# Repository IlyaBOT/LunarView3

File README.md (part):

# Lunar Dumper / Lunar Writer

Актуальные устройства проекта:

- **[Lunar Dumper](Dumper-Lite/NM27C512_Dumper_Lite.kicad_pro)** — минимальный USB-дампер, 5 В, чтение EPROM. Пользовательская разводка сохранена; обновлены названия и идентификатор прошивки. [Инструкция](Dumper-Lite/README.md), [прошивка 115200](firmware/lite/README.md).
- **[Lunar Writer, Rev. 1](Lunar-Writer/Lunar_Writer.kicad_pro)** — новая полностью разведённая двухслойная плата **150×105 мм**, ATmega/CH340/DIP-28, буфер данных, коммутация VCC/VPP и отдельная винтовая клемма **12–24 В DC**. [Описание и настройка](Lunar-Writer/README.md), [схема PDF](Lunar-Writer/Lunar_Writer_Schematic.pdf), [3D](Lunar-Writer/Writer_3D.png), [Gerber/drill](Lunar-Writer/production/). ERC/DRC/соответствие схеме: 0 замечаний; 0 неразведённых связей. Аппаратная наладка ещё не выполнена, штатная WRITE заблокирована.
- **[LunarView 3, 1.2](app-win_forms/README.md)** — Windows Forms: чтение, HEX/ASCII, открытие ROM-файлов и сравнение. Сборка: `app-win_forms/release/LunarView3.exe`. Сейчас работает с протоколом Lunar Dumper; Writer обслуживается прежней утилитой `tools/eprom_tool.py`, 57600 бод.
- **[Адаптер КР573РФ5](Adapter-KR573RF5/README.md)** — отдельная плата только для чтения, не для программирования через Writer.
- [Изготовление фоторезистом](docs/PCB_Photoresist_RU.md), [источники 3D-моделей](docs/3D_Models_RU.md).

Проверка от 12.10.2026: новую плату Writer проверили отдельно. У сохранённого пользовательского Dumper остаются прежние 2 неразведённые связи и 16 предупреждений (15 изолированных участков меди, 1 незавершённая дорожка); переименование их не изменило. До домашнего изготовления Dumper следует закончить эту проверку. Медные слои и геометрия Dumper при работе над Writer не менялись; доказательство — `validation/lunar-products-2026-10-12/rename-audit.json`.

Файлы `NM27C512_Dumper.*` в корне и `baseline_readonly/` сохранены как исторические проекты Stage 2 / раннего read-only. Полноценный актуальный программатор открывается из **Lunar-Writer**. Ниже приведены сведения старой Stage 2: там J4 являлся входом готового VPP, а повышающего преобразователя не было. Для нового питания и калибровки Writer используйте его README.

## Historical Stage 2 architecture

```mermaid
flowchart LR
    USB[USB Micro-B 5 V] --> F[F1 and 5 V logic rail]
    USB --> CH[CH340C USB UART]
    CH <--> AVR[ATmega328P 16 MHz]
    AVR --> SR[U2/U3/U4 74HC595 chain]
    SR --> A[A0-A19 and RGB status]
    AVR <--> H[Protected HCT245 data bus]
    H <--> ROM[U6 NM27C512 or one J_TARGET adapter]
    A --> ROM
    EXT[External regulated VPP] --> ARM[Q3 PMOS arming stage]
    ARM --> PULSE[Q7 final VPP switch]
    EXT --> REG[LM317 6.25 V]
    REG --> K[K1 default-READ DPDT relay]
    PULSE --> K
    F --> K
    K --> ROM
    RESET[RESET and enable gates] --> ARM
    RESET --> PULSE
    AVR --> K
```

USB supplies all 5 V logic, the CH340 and relay. J4 accepts regulated VPP_IN on pin1 and GND on pin2, expected 12.5-25 V depending on the exact profile. +6V25_PROG is generated from that supply with LM317T. K1 selects target +5 V / +6.25 V and separately selects socket pin22 OE logic / VPP_SW. Normal RESET and power-on use the unenergized READ contacts. VPP and elevated target VCC have no direct connection to an AVR GPIO.

Old NMOS EPROMs can have TTL output-high specifications below the AVR's 5 V CMOS input threshold. Stage 2 therefore uses **SN74HCT245DW**, with TTL-compatible inputs; a 74HC245 is not an equivalent substitute here. Both sides have 1k resistors and external BAT54S clamps. The read-only baseline keeps the requested direct NM27C512 data connection. Target outputs during 6.25 V byte verify are clamped on the buffer side. MCU releases its outputs before VPP_DRIVE changes the bus direction.

## ATmega328P-AU TQFP32 map

PB1, originally reserved for an interlock, now explicitly controls HV_ARM_EN. PB4/MISO is used only by ISP. ADC6/ADC7 are analog-only package pins.

| Package pin | Function | Net |
| --- | --- | --- |
| 1 | PD3 | PROG_MODE |
| 2 | PD4 | ROM_D6 |
| 3 | GND | GND |
| 4 | VCC | +5V |
| 5 | GND | GND |
| 6 | VCC | +5V |
| 7 | PB6 / XTAL1 | XTAL1 |
| 8 | PB7 / XTAL2 | XTAL2 |
| 9 | PD5 | ROM_D7 |
| 10 | PD6 | TARGET_CE_PGM# |
| 11 | PD7 | TARGET_OE# |
| 12 | PB0 | TARGET_PGM# |
| 13 | PB1 | HV_ARM_EN |
| 14 | PB2 | ADDR_LATCH |
| 15 | PB3 / MOSI | ADDR_SER |
| 16 | PB4 / MISO | ISP_MISO |
| 17 | PB5 / SCK | ADDR_SCK |
| 18 | AVCC | +5V |
| 19 | ADC6 | VPP_SENSE |
| 20 | AREF | AREF |
| 21 | GND | GND |
| 22 | ADC7 | TARGET_VCC_SENSE |
| 23 | PC0 | ROM_D0 |
| 24 | PC1 | ROM_D1 |
| 25 | PC2 | ROM_D2 |
| 26 | PC3 | ROM_D3 |
| 27 | PC4 | ROM_D4 |
| 28 | PC5 | ROM_D5 |
| 29 | PC6 / RESET | RESET |
| 30 | PD0 / RXD | UART_RX |
| 31 | PD1 / TXD | UART_TX |
| 32 | PD2 | VPP_EN |

## Address and status chain

U2 SER is PB3/MOSI. U2 Q7S (pin9) goes to U3 SER (pin14), then U3 Q7S to U4 SER. All three share pin11 SRCLK=ADDR_SCK/PB5 and pin12 RCLK=ADDR_LATCH/PB2; SRCLR# pin10=+5V, OE# pin13=GND, VCC16=+5V and GND8=GND. R7 pulls LATCH down during RESET/ISP, keeping ISP shifts from latching. CE/OE/PGM pull-ups keep the target inactive while addresses are unspecified at initial power-up.

| Output | U2 | U3 | U4 |
|---|---|---|---|
| Q0 / pin15 | A0 | A8 | A16 |
| Q1 / pin1 | A1 | A9 | A17 |
| Q2 / pin2 | A2 | A10 | A18 |
| Q3 / pin3 | A3 | A11 | A19 |
| Q4 / pin4 | A4 | A12 | STATUS_RED |
| Q5 / pin5 | A5 | A13 | STATUS_GREEN |
| Q6 / pin6 | A6 | A14 | STATUS_BLUE |
| Q7 / pin7 | A7 | A15 | NC / reserved |

Send U4 byte first, U3 next and U2 last, MSB first, then latch. The high byte's low nibble is A16-A19; bits4/5/6 are active-low RGB R/G/B; bit7 remains LOW. Firmware preserves RGB state on every address update and masks unused upper addresses LOW for smaller profiles. The baseline sends only U3 then U2.

## Direct U6 socket: NM27C512 DIP28

Use only a correctly oriented NM27C512 or verified compatible read part in U6. Footprint is `Package_DIP:DIP-28_W15.24mm_Socket_LongPads`; it suits a conventional 600 mil socket. Verify the selected ZIF socket's body/lever clearance before PCB layout rather than assuming every ZIF is mechanically identical.

| Pin | Net | Pin | Net |
| --- | --- | --- | --- |
| 1 | A15 | 28 | TARGET_VCC |
| 2 | A12 | 27 | A14 |
| 3 | A7 | 26 | A13 |
| 4 | A6 | 25 | A8 |
| 5 | A5 | 24 | A9 |
| 6 | A4 | 23 | A11 |
| 7 | A3 | 22 | SOCKET_OE_VPP |
| 8 | A2 | 21 | A10 |
| 9 | A1 | 20 | TARGET_CE_PGM# |
| 10 | A0 | 19 | TARGET_D7 |
| 11 | TARGET_D0 | 18 | TARGET_D6 |
| 12 | TARGET_D1 | 17 | TARGET_D5 |
| 13 | TARGET_D2 | 16 | TARGET_D4 |
| 14 | GND | 15 | TARGET_D3 |

In READ, TARGET_VCC=+5V and SOCKET_OE_VPP follows TARGET_OE#. In PROGRAM, TARGET_VCC=+6.25V and SOCKET_OE_VPP=VPP_SW. Pin20 CE/PGM# is the programming-pulse input. R2/R3/R8 pull CE/OE/PGM HIGH from the logic rail during RESET. K1 physically disconnects the MCU OE path from VPP.

## Headers and UART

J2 is the standard AVR ISP 2x3: pin1 MISO, 2 +5V, 3 SCK, 4 MOSI, 5 RESET, 6 GND. J3 is a 1x3 header: **1 GND, 2 RX (MCU PD0), 3 TX (MCU PD1)**. An external UART TX goes to J3 RX and external RX to J3 TX. Use 5 V TTL and avoid simultaneous active TX sources.

CH340C TXD pin2 goes through R4=1k to MCU RX; MCU TX goes through R5=1k to CH340 RXD pin3. WCH pins: 1 GND, 4 V3 (C3 only), 5 UD+, 6 UD-, 7 NC, 8 OUT#/optional DTR2 (unused), 9 CTS#, 10 DSR#, 11 RI#, 12 DCD#, 13 DTR#, 14 RTS#, 15 R232=GND, 16 VCC=+5V. Every unused output/input has an explicit NC marker. CH340C has an internal oscillator: there is no 12 MHz crystal.

DTR# reaches RESET through C13=100nF, not directly. R1 is the 10k 0603 pull-up, SW1 resets to GND, and ISP RESET is the same net. D9 clamps a positive DTR-release spike on RESET, which also feeds the 5 V interlock inputs.

J1 uses `Connector_USB:USB_Micro-B_Molex-105017-0001`; buy that pad-compatible receptacle. Pins1/2/3/4/5 are VBUS/D-/D+/NC/GND. Shield pad SH=GND. USB VBUS reaches the logic rail through the 1812 500 mA hold polyfuse. The complete circuit can exceed 100 mA, especially with an old EPROM and the 100 mA relay coil. Use a stable USB source whose permitted current covers the load; assess USB descriptor/current and inrush compliance during product engineering. The polyfuse is not an active inrush limiter.

## J_TARGET 2x20 expansion pinout

Odd numbers are the symbol's left column; even numbers are right. Data pins expose the protected **target side** of U9, not the bare MCU pins. Populate U6 or one adapter, never both.

| Odd pin | Net | Even pin | Net |
| --- | --- | --- | --- |
| 1 | A0 | 2 | A1 |
| 3 | A2 | 4 | A3 |
| 5 | A4 | 6 | A5 |
| 7 | A6 | 8 | A7 |
| 9 | A8 | 10 | A9 |
| 11 | A10 | 12 | A11 |
| 13 | A12 | 14 | A13 |
| 15 | A14 | 16 | A15 |
| 17 | A16 | 18 | A17 |
| 19 | A18 | 20 | A19 |
| 21 | TARGET_D0 | 22 | TARGET_D1 |
| 23 | TARGET_D2 | 24 | TARGET_D3 |
| 25 | TARGET_D4 | 26 | TARGET_D5 |
| 27 | TARGET_D6 | 28 | TARGET_D7 |
| 29 | TARGET_CE_PGM# | 30 | TARGET_OE# |
| 31 | TARGET_PGM# | 32 | VPP_SW |
| 33 | TARGET_VCC | 34 | +5V |
| 35 | +6V25_PROG | 36 | GND |
| 37 | PROG_MODE | 38 | GND |
| 39 | RESET | 40 | GND |

Adapters are device-specific. The three reference sheets document 24/28/32-pin roles without adding multiple live EPROM loads. Separate VPP pins often need +5 V in READ, so do not tie them to an unpowered VPP_SW. Future programming adapters require appropriately rated switching or keyed jumpers; the onboard K1 switches U6 pin22 only. RF5 mapping is intentionally withheld pending a manufacturer source.

## VPP, relay and regulator details

Q3 IRF9540N is a 100 V P-channel TO220 device, G1/D2/S3. R30 pulls gate to source; Q4 pulls the gate through R31=2.2k. D5's cathode is SOURCE/VPP_IN and anode is GATE, limiting |VGS| to approximately 10 V. The gate resistor is 1206 / at least 0.25 W for the worst input, instead of overstressing a small resistor. U10 gates PB1 with RESET for arming; U8 gates PD2 with RESET for the final VPP switch. Pull-downs keep both OFF when AVR pins float. No onboard 5-to-25 V boost is present.

The slow PMOS arms an internal node; Q7 MMBT5401 / Q6 MMBT5551 provide the separate final VPP switch. This is a prototype pulse-stage choice; its <=50 ns OE/VPP rise requirement is **unverified** and must be measured before WRITE is commissioned. Its voltage drop must be calibrated at load. No bulk cap sits on VPP_SW; R37=10k discharges it. D6 and two 5.1k resistors indicate actual switched VPP independently of the software RGB LED.

K1 standard G5V-2-DC5 uses coil pins1/16, COM4-NC6-NO8 for VCC and COM13-NC11-NO9 for OE/VPP. Q5 drives the 100 mA coil; R42=470 ohm gives roughly 9 mA base drive. This replaces the suggested 10k value, which would not establish saturation for that coil. D8 is the 1N4148WS SOD323 flyback diode, cathode on +5V.

LM317T pin1 ADJ, 2 OUT, 3 IN. R40=120 ohm, R41=430 ohm and RV1=100 ohm set +6V25_PROG. Measure and adjust TP_6V25 to 6.250 V, then verify under load. Approximately 48 ohm of trim is nominal; real reference/Iadj vary. A heatsink is needed for the intended high-input/load combination. Details and acceptance tests are in [bringup.md](docs/bringup.md).

## Voltage monitoring

ADC6 divider is 120k/22k, both 1%, with 10nF at the node: `Vadc = VPP_SW * 22 / 142`. ADC7 is a 10k/10k, 1% divider with 10nF: 5 V target gives 2.500 V and 6.25 V gives 3.125 V. D30/D31 add external Schottky clamps at the ADC nodes.

| VPP_SW, V | Nominal ADC6, V |
| --- | --- |
| 12.75 | 1.975352 |
| 21 | 3.253521 |
| 25 | 3.873239 |
| 30 | 4.647887 |

At 30 V, worst 1% divider tolerance (118.8k top / 22.22k bottom) gives 4.726989 V, below the firmware's 4.75 V minimum logic rail. Normal external supply maximum is 25 V. These are divider ratings, not permitted NM27C512 programming voltages. The calibrated ADC must enforce that profile's much narrower 12.50-13.00 V window. ADC filtering cannot certify transient overshoot; the socket waveform must be scoped.

## Indicators and test points

| Indicator | Meaning |
|---|---|
| D2 GREEN | READ / VERIFY state |
| D2 RED | WRITE state |
| D2 AMBER | IDLE (red and green) |
| D2 BLUE | Transfer/program error state |
| D3 BLUE | Actual UART RX LOW bits via Q1 |
| D4 ORANGE | Actual UART TX LOW bits via Q2 |
| D6 RED | Actual VPP_SW present |

D2 uses the project-local combined common-anode RGB footprint: square SMD KAAF-5050RGBS-13 or four-lead THT WP154A4SEJ3VBDZGW/CA. Populate **one LED only**. Logical pad numbering is 1R/2A/3G/4B; manufacturer numbering differs. See [mounting and pin mapping](docs/RGB_Mounting.md). Each colour has 1k to the relevant 595 output, LOW=ON. Q1/Q2 MMBT3906 emitters are +5V; 10k base resistors limit UART loading to roughly 0.4 mA during LOW bits and LEDs are OFF at idle HIGH. Their collectors drive LEDs through 1k; they do not put a heavy direct LED load on UART.

TP1-TP13 are respectively 5V, GND, 6V25, VPP_IN, VPP_SW, RESET, ADDR_SCK, ADDR_LATCH, CE, OE, PGM, RX and TX. Each is named on its schematic page and is a 1.5 mm pad footprint.

## Device support matrix

The hardware column describes routed schematic capability; no adapter or board has been physically validated. Read verification and algorithm verification have separate source/implementation meanings.

| Device profile | KiB | Address bits | Hardware electrically supported (schematic) | Read profile | Programming algorithm |
| --- | --- | --- | --- | --- | --- |
| NM27C512 | 64 | 16 | Yes, U6 | Enabled | Verified; default bench lock |
| 27C512 | 64 | 16 | Yes, U6 | Enabled | Disabled |
| INTEL2716 | 2 | 11 | Yes, matching adapter | Enabled | Disabled |
| INTEL2732 | 4 | 12 | Yes, matching adapter | Enabled | Disabled |
| INTEL2764 | 8 | 13 | Yes, matching adapter | Enabled | Disabled |
| INTEL27128A | 16 | 14 | Yes, matching adapter | Enabled | Disabled |
| INTEL27256 | 32 | 15 | Yes, matching adapter | Enabled | Disabled |
| KR573RF5 | 2 | 11 | Pending pinout | Disabled/pending | Disabled |
| NM27C010 | 128 | 17 | Yes, matching adapter | Enabled | Disabled |
| NM27C020 | 256 | 18 | Yes, matching adapter | Enabled | Disabled |
| NM27C040 | 512 | 19 | Yes, matching adapter | Enabled | Disabled |
| NM27C080 | 1024 | 20 | Address/pin-role basis | Disabled/pending | Disabled |

2708 is unsupported: its normal read needs +12 V and -5 V in addition to +5 V. 27C160 is unsupported: it requires a 16-bit bus. Different manufacturers' programming rails/polarities/timings must be separate profiles; generic aliases do not authorize WRITE.

## Firmware and host use

Bare-metal AVR C implements INFO, LIST, READ, VERIFY, WRITE and VOLTAGES. Profile size/address mask and program voltage/pulse parameters come from the generated flash table. Timer1 generates the nominal 100 us CE pulse; Timer0 handles the timeouts. Watchdog is 1 s. Hardware RESET gates cut both VPP switches even while AVR GPIO state changes; software turns off VPP before returning the relay to READ. Link/CRC/UART errors invoke the safe sequence. [Protocol details](docs/protocol.md) include the frames, keepalive and final whole-image CRC.

Default WRITE is locked. The National algorithm implemented for NM27C512 requires an erased device, 6.25 V VCC, 12.75 V VPP, 100 us pulses with up to 25 attempts, per-byte verify and final comparison at 5 V. The host requires ambient 20-30 C and explicit confirmation. It checks actual switched VPP with the socket isolated before selecting PROGRAM, then target VCC and VPP before pulses. The circuit must pass [bench commissioning](docs/bringup.md) before using a commissioned build. Do not insert/remove devices while either supply is connected.

```powershell
# Build the default read/verify firmware (WRITE locked).
./firmware/build.ps1

# Install the host's serial dependency; listing itself works without pyserial.
python -m pip install -r tools/requirements.txt
python tools/eprom_tool.py list
python tools/eprom_tool.py info --port COM5
python tools/eprom_tool.py voltages --port COM5
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
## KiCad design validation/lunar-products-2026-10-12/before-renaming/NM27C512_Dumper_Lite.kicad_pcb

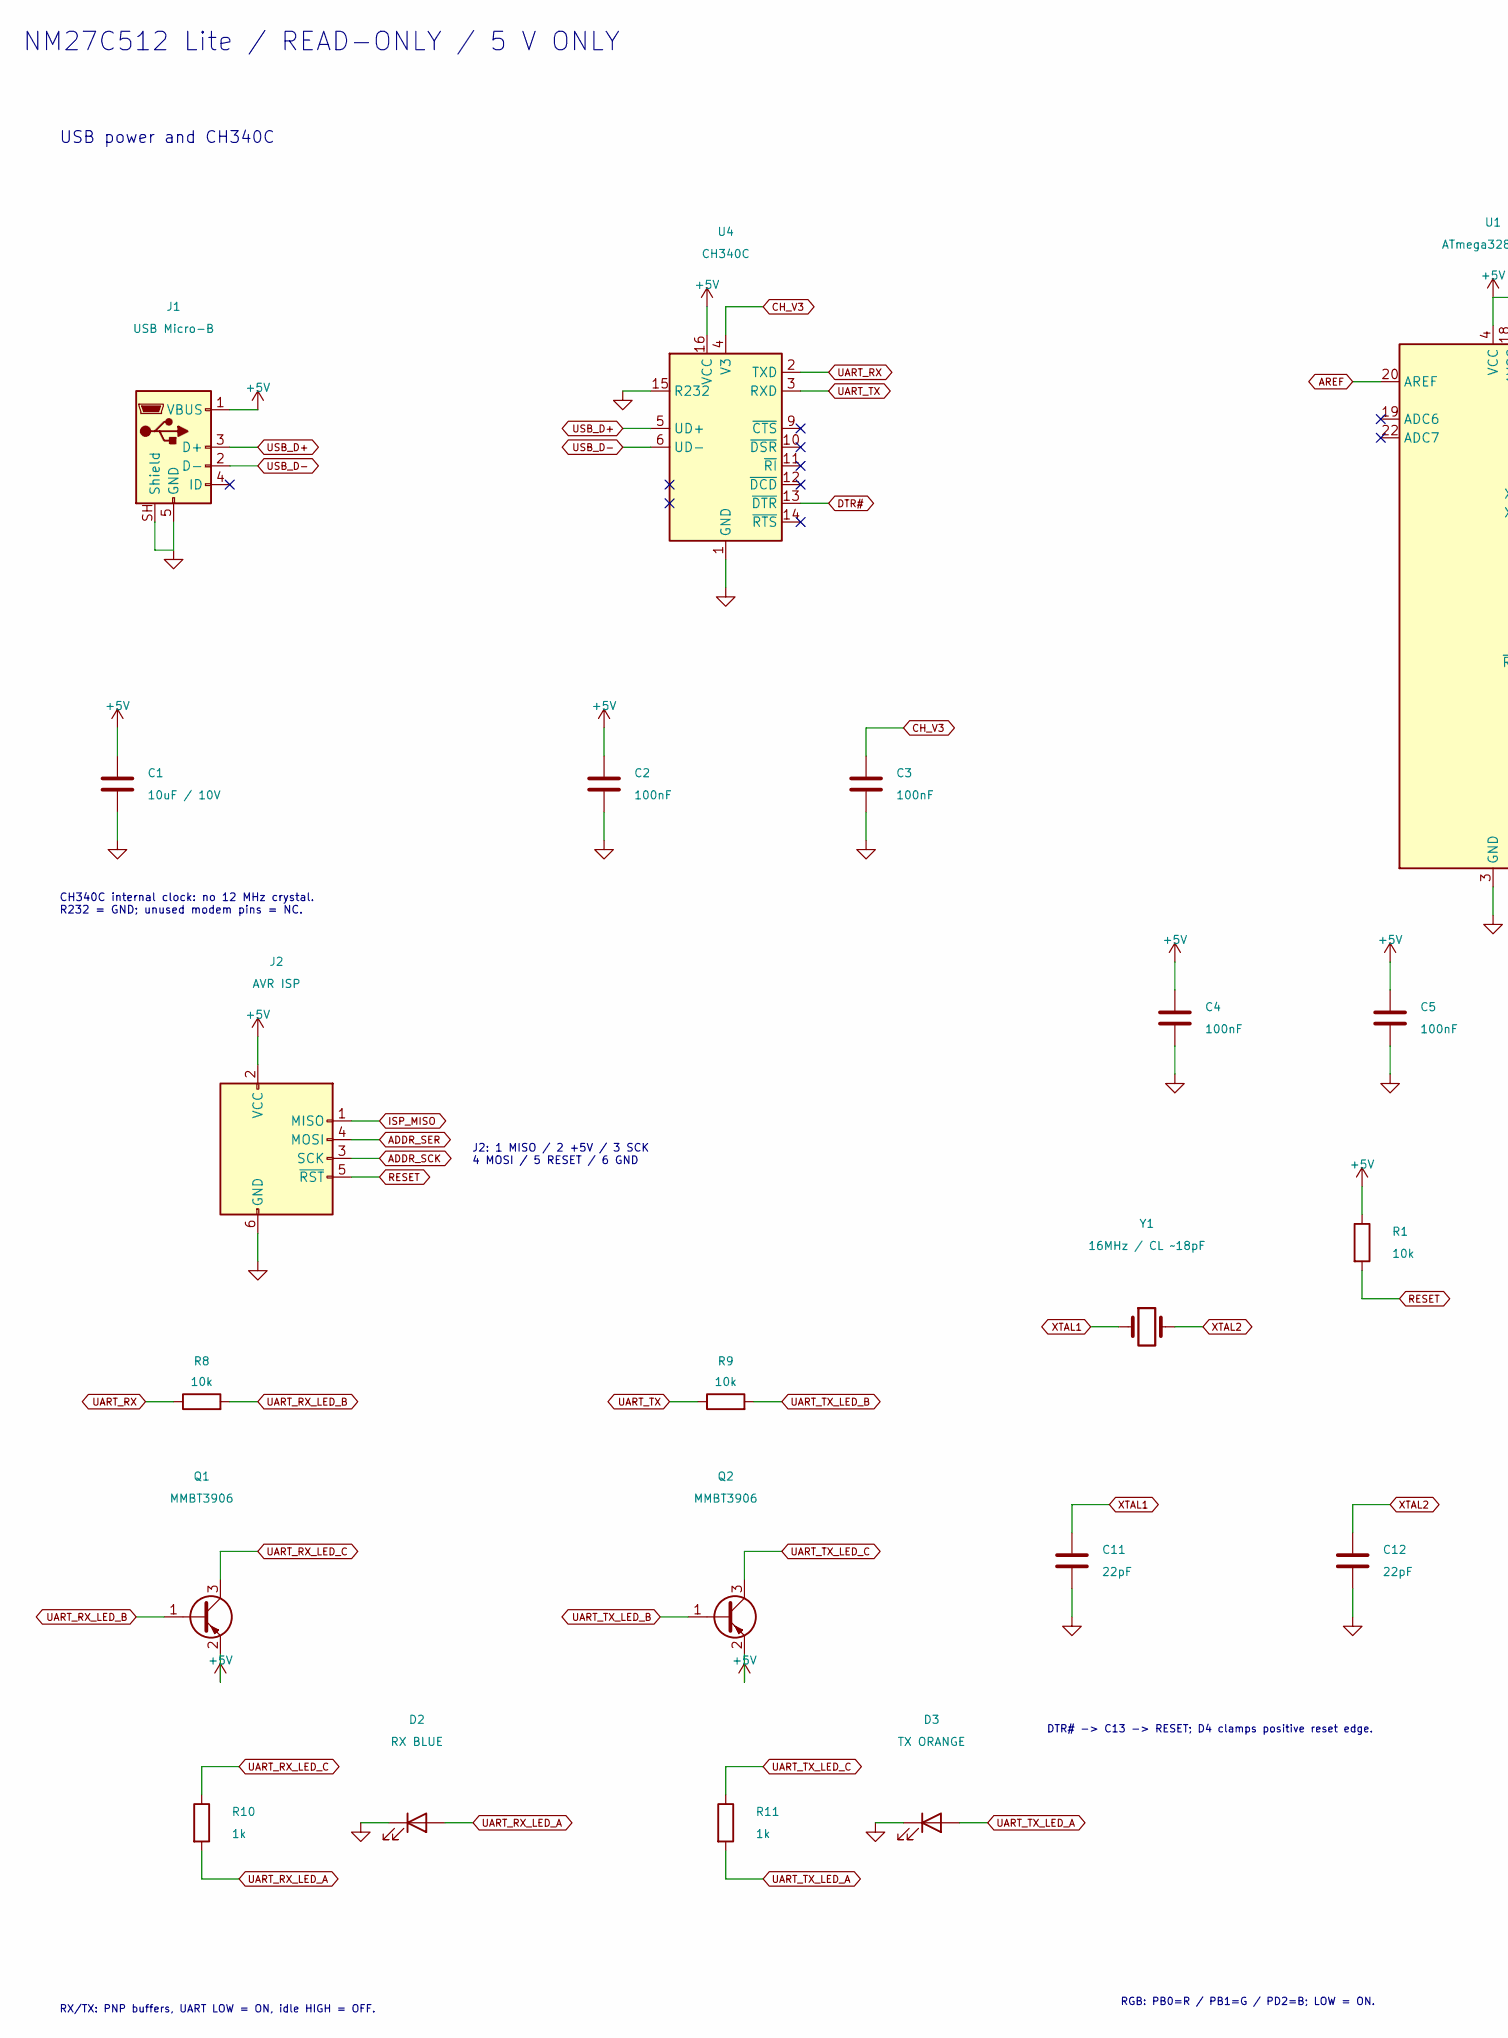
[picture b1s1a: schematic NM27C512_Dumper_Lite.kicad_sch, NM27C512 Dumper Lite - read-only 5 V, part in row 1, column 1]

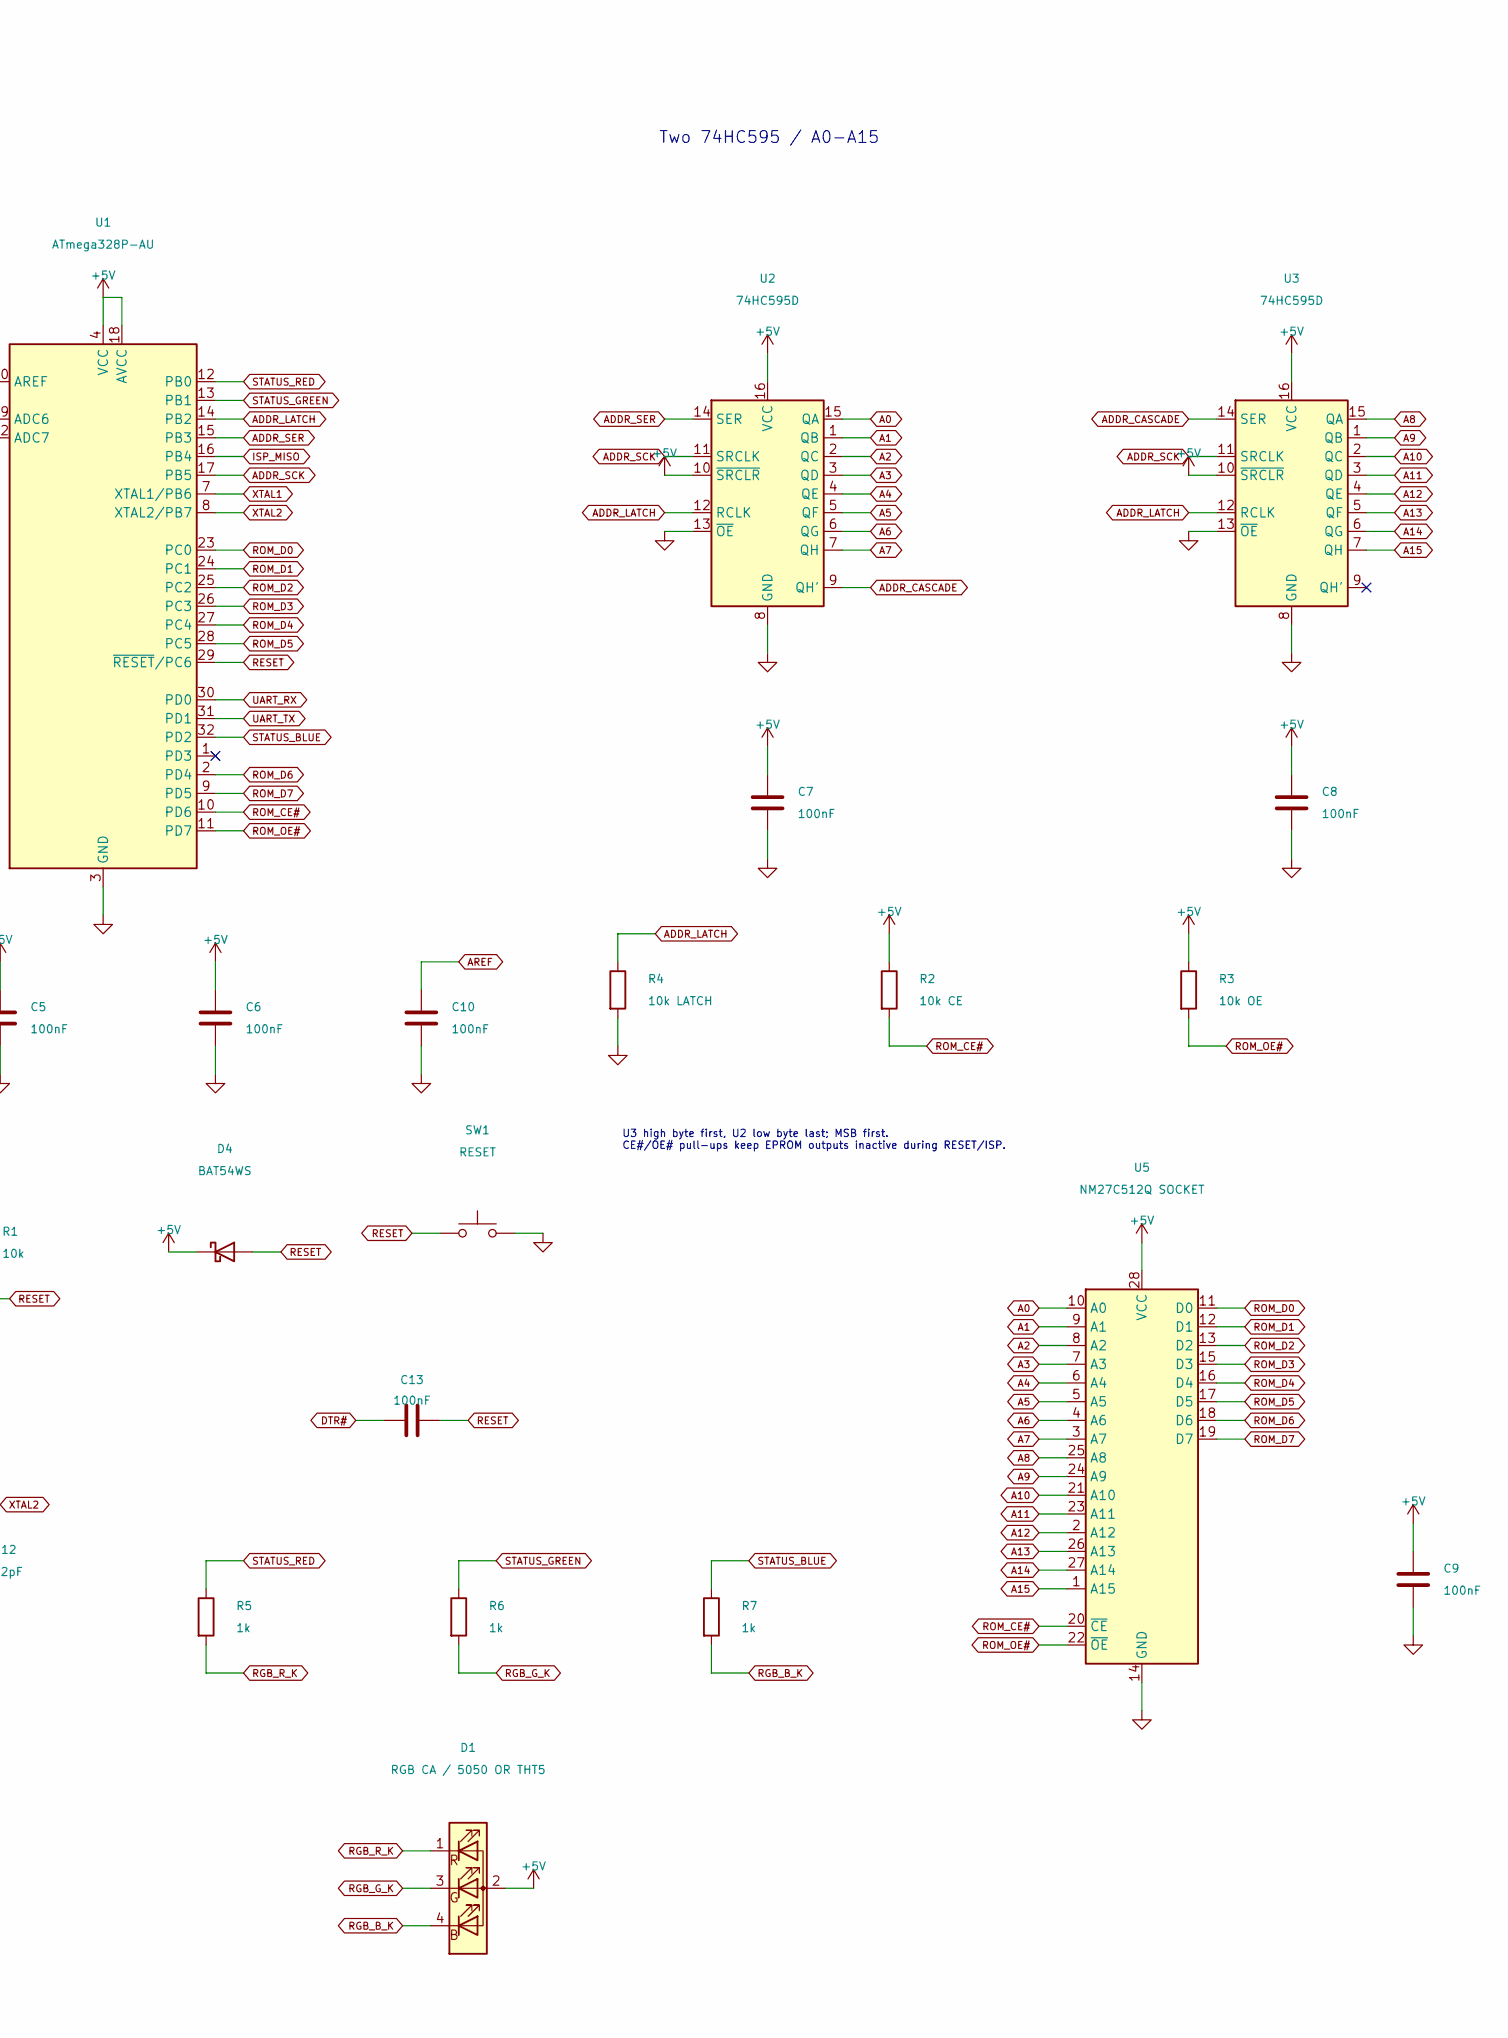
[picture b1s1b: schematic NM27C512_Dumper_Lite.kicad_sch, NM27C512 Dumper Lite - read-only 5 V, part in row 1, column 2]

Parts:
C1: 10uF / 10V; C_0805_2012Metric
C2, C3, C4, C5, C6, C7, C8, C9, C10, C13: 100nF; C_0603_1608Metric
C11, C12: 22pF; C_0603_1608Metric
D1: RGB CA / 5050 OR THT5; RGB_CA_5050_or_THT5
D2: RX BLUE; LED_0603_1608Metric
D3: TX ORANGE; LED_0603_1608Metric
D4: BAT54WS; D_SOD-323
J1: USB Micro-B; USB_Micro-B_Molex-105017-0001
J2: AVR ISP; PinHeader_2x03_P2.54mm_Vertical
Q1, Q2: MMBT3906; SOT-23
R1, R8, R9: 10k; R_0603_1608Metric
R2: 10k CE; R_0603_1608Metric
R3: 10k OE; R_0603_1608Metric
R4: 10k LATCH; R_0603_1608Metric
R5, R6, R7, R10, R11: 1k; R_0603_1608Metric
SW1: RESET; SW_PUSH_6mm
U1: ATmega328P-AU; TQFP-32_7x7mm_P0.8mm
U2, U3: 74HC595D; SOIC-16_3.9x9.9mm_P1.27mm
U4: CH340C; SOIC-16_3.9x9.9mm_P1.27mm
U5: NM27C512Q SOCKET; DIP-28_W15.24mm_Socket_LongPads
Y1: 16MHz / CL ~18pF; Crystal_HC49-4H_Vertical

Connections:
+5V: C1.1, C2.1, C4.1, C5.1, C6.1, C7.1, C8.1, C9.1, D1.2 (A), D4.1 (K), J1.1 (VBUS), J2.2 (VCC), Q1.2 (E), Q2.2 (E), R1.1, R2.1, R3.1, U1.4 (VCC), U1.6 (VCC), U1.18 (AVCC), U2.10 (~SRCLR), U2.16 (VCC), U3.10 (~SRCLR), U3.16 (VCC), U4.16 (VCC), U5.28 (VCC)
A0: U2.15 (QA), U5.10 (A0)
A1: U2.1 (QB), U5.9 (A1)
A2: U2.2 (QC), U5.8 (A2)
A3: U2.3 (QD), U5.7 (A3)
A4: U2.4 (QE), U5.6 (A4)
A5: U2.5 (QF), U5.5 (A5)
A6: U2.6 (QG), U5.4 (A6)
A7: U2.7 (QH), U5.3 (A7)
A8: U3.15 (QA), U5.25 (A8)
A9: U3.1 (QB), U5.24 (A9)
A10: U3.2 (QC), U5.21 (A10)
A11: U3.3 (QD), U5.23 (A11)
A12: U3.4 (QE), U5.2 (A12)
A13: U3.5 (QF), U5.26 (A13)
A14: U3.6 (QG), U5.27 (A14)
A15: U3.7 (QH), U5.1 (A15)
ADDR_CASCADE: U2.9 (QH'), U3.14 (SER)
ADDR_LATCH: R4.1, U1.14 (PB2), U2.12 (RCLK), U3.12 (RCLK)
ADDR_SCK: J2.3 (SCK), U1.17 (PB5), U2.11 (SRCLK), U3.11 (SRCLK)
ADDR_SER: J2.4 (MOSI), U1.15 (PB3), U2.14 (SER)
AREF: C10.1, U1.20 (AREF)
CH_V3: C3.1, U4.4 (V3)
DTR#: C13.1, U4.13 (~DTR)
GND: C1.2, C2.2, C3.2, C4.2, C5.2, C6.2, C7.2, C8.2, C9.2, C10.2, C11.2, C12.2, D2.1 (K), D3.1 (K), J1.5 (GND), J1.SH (Shield), J2.6 (GND), R4.2, SW1.2, U1.3 (GND), U1.5 (GND), U1.21 (GND), U2.8 (GND), U2.13 (~OE), U3.8 (GND), U3.13 (~OE), U4.1 (GND), U4.15 (R232), U5.14 (GND)
ISP_MISO: J2.1 (MISO), U1.16 (PB4)
RESET: C13.2, D4.2 (A), J2.5 (~RST), R1.2, SW1.1, U1.29 (~RESET/PC6)
RGB_B_K: D1.4 (B), R7.2
RGB_G_K: D1.3 (G), R6.2
RGB_R_K: D1.1 (R), R5.2
ROM_CE#: R2.2, U1.10 (PD6), U5.20 (~CE)
ROM_D0: U1.23 (PC0), U5.11 (D0)
ROM_D1: U1.24 (PC1), U5.12 (D1)
ROM_D2: U1.25 (PC2), U5.13 (D2)
ROM_D3: U1.26 (PC3), U5.15 (D3)
ROM_D4: U1.27 (PC4), U5.16 (D4)
ROM_D5: U1.28 (PC5), U5.17 (D5)
ROM_D6: U1.2 (PD4), U5.18 (D6)
ROM_D7: U1.9 (PD5), U5.19 (D7)
ROM_OE#: R3.2, U1.11 (PD7), U5.22 (~OE)
STATUS_BLUE: R7.1, U1.32 (PD2)
STATUS_GREEN: R6.1, U1.13 (PB1)
STATUS_RED: R5.1, U1.12 (PB0)
UART_RX: R8.1, U1.30 (PD0), U4.2 (TXD)
UART_RX_LED_A: D2.2 (A), R10.2
UART_RX_LED_B: Q1.1 (B), R8.2
UART_RX_LED_C: Q1.3 (C), R10.1
UART_TX: R9.1, U1.31 (PD1), U4.3 (RXD)
UART_TX_LED_A: D3.2 (A), R11.2
UART_TX_LED_B: Q2.1 (B), R9.2
UART_TX_LED_C: Q2.3 (C), R11.1
USB_D+: J1.3 (D+), U4.5 (UD+)
USB_D-: J1.2 (D-), U4.6 (UD-)
XTAL1: C11.1, U1.7 (XTAL1/PB6), Y1.1
XTAL2: C12.1, U1.8 (XTAL2/PB7), Y1.2

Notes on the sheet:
RX/TX: PNP buffers, UART LOW = ON, idle HIGH = OFF.
RGB: PB0=R / PB1=G / PD2=B; LOW = ON.
U3 high byte first, U2 low byte last; MSB first. CE#/OE# pull-ups keep EPROM outputs inactive during RESET/ISP.
USB power and CH340C
NM27C512 Lite / READ-ONLY / 5 V ONLY
CH340C internal clock: no 12 MHz crystal. R232 = GND; unused modem pins = NC.
Two 74HC595 / A0-A15
DTR# -> C13 -> RESET; D4 clamps positive reset edge.
J2: 1 MISO / 2 +5V / 3 SCK 4 MOSI / 5 RESET / 6 GND

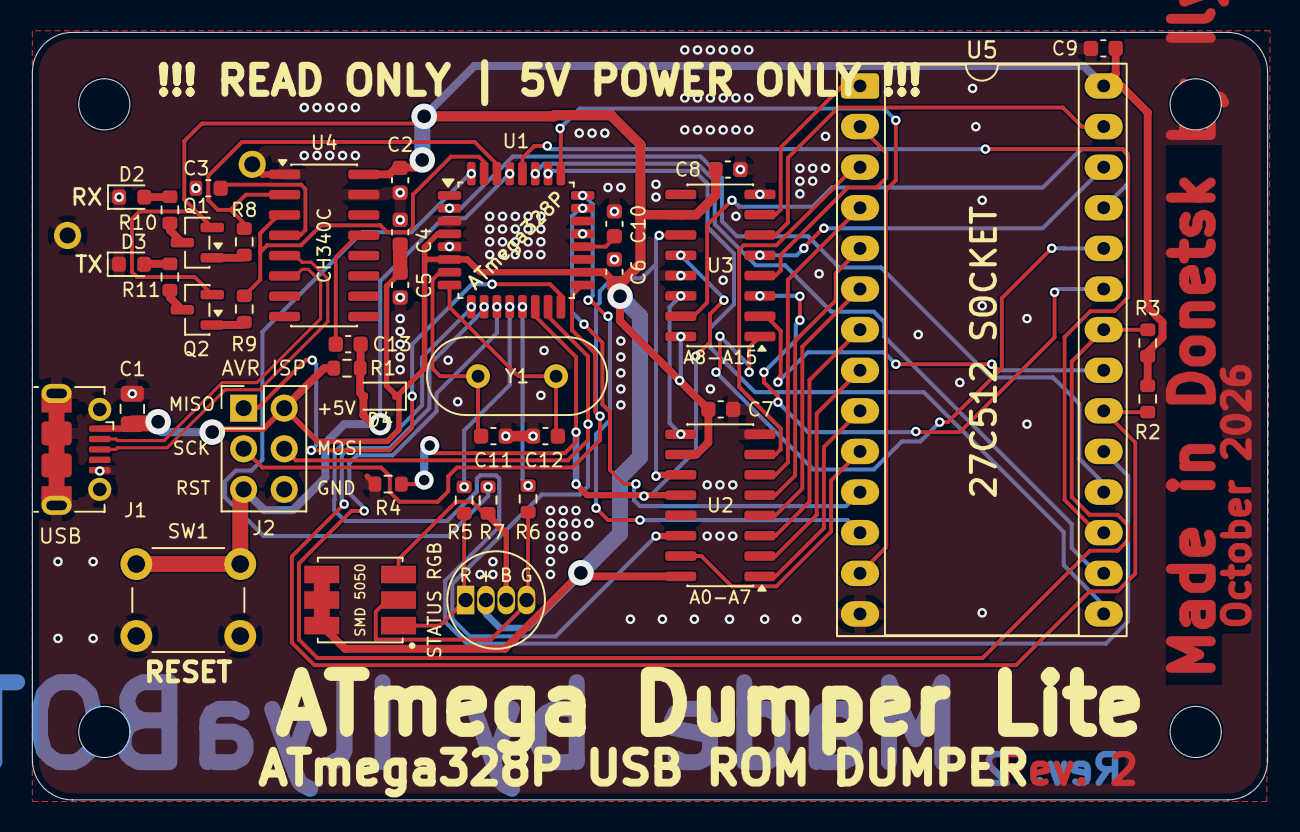
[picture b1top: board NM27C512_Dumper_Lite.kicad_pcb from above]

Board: 2 copper layers, 77.2 x 48.0 mm, 43 parts (0 on the bottom side), 55 nets.

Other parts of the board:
H1, H2, H3, H4: M3 mounting hole; MountingHole_3.2mm_M3

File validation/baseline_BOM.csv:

ref,value,symbol,footprint,sheet
J1,USB Micro-B,Connector:USB_B_Micro,Connector_USB:USB_Micro-B_Molex-105017-0001,controller.kicad_sch
F1,500mA hold,Device:Polyfuse,Fuse:Fuse_1812_4532Metric,controller.kicad_sch
C1,10uF / 10V,Device:C,Capacitor_SMD:C_0805_2012Metric,controller.kicad_sch
U4,CH340C,ProjectSymbols:CH340C_WCH,Package_SO:SOIC-16_3.9x9.9mm_P1.27mm,controller.kicad_sch
C2,100nF,Device:C,Capacitor_SMD:C_0603_1608Metric,controller.kicad_sch
C3,100nF,Device:C,Capacitor_SMD:C_0603_1608Metric,controller.kicad_sch
R4,1k,Device:R,Resistor_SMD:R_0603_1608Metric,controller.kicad_sch
R5,1k,Device:R,Resistor_SMD:R_0603_1608Metric,controller.kicad_sch
U1,ATmega328P-AU,MCU_Microchip_ATmega:ATmega328P-A,Package_QFP:TQFP-32_7x7mm_P0.8mm,controller.kicad_sch
Y1,"16MHz, CL ~18pF",Device:Crystal,Crystal:Crystal_HC49-4H_Vertical,controller.kicad_sch
C11,22pF,Device:C,Capacitor_SMD:C_0603_1608Metric,controller.kicad_sch
C12,22pF,Device:C,Capacitor_SMD:C_0603_1608Metric,controller.kicad_sch
R1,10k,Device:R,Resistor_SMD:R_0603_1608Metric,controller.kicad_sch
SW1,RESET,Switch:SW_Push,Button_Switch_THT:SW_PUSH_6mm,controller.kicad_sch
C13,100nF auto-reset,Device:C,Capacitor_SMD:C_0603_1608Metric,controller.kicad_sch
C4,100nF,Device:C,Capacitor_SMD:C_0603_1608Metric,controller.kicad_sch
C5,100nF,Device:C,Capacitor_SMD:C_0603_1608Metric,controller.kicad_sch
C6,100nF,Device:C,Capacitor_SMD:C_0603_1608Metric,controller.kicad_sch
C10,100nF,Device:C,Capacitor_SMD:C_0603_1608Metric,controller.kicad_sch
J2,AVR ISP,Connector:AVR-ISP-6,Connector_PinHeader_2.54mm:PinHeader_2x03_P2.54mm_Vertical,controller.kicad_sch
J3,UART (MCU RX/TX),Connector_Generic:Conn_01x03,Connector_PinHeader_2.54mm:PinHeader_1x03_P2.54mm_Vertical,controller.kicad_sch
U2,74HC595D,74xx:74HC595,Package_SO:SOIC-16_3.9x9.9mm_P1.27mm,address_target.kicad_sch
C7,100nF,Device:C,Capacitor_SMD:C_0603_1608Metric,address_target.kicad_sch
U3,74HC595D,74xx:74HC595,Package_SO:SOIC-16_3.9x9.9mm_P1.27mm,address_target.kicad_sch
C8,100nF,Device:C,Capacitor_SMD:C_0603_1608Metric,address_target.kicad_sch
R7,10k LATCH pull-down,Device:R,Resistor_SMD:R_0603_1608Metric,address_target.kicad_sch
U5,NM27C512Q SOCKET,Memory_EPROM:27C512,Package_DIP:DIP-28_W15.24mm_Socket_LongPads,address_target.kicad_sch
C9,100nF / 16V,Device:C,Capacitor_SMD:C_0603_1608Metric,address_target.kicad_sch
R2,10k CE pull-up,Device:R,Resistor_SMD:R_0603_1608Metric,address_target.kicad_sch
R3,10k OE pull-up,Device:R,Resistor_SMD:R_0603_1608Metric,address_target.kicad_sch
R6,1k,Device:R,Resistor_SMD:R_0603_1608Metric,address_target.kicad_sch
D1,POWER GREEN,Device:LED,LED_SMD:LED_0603_1608Metric,address_target.kicad_sch

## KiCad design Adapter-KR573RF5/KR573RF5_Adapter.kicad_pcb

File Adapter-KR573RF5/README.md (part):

# Компактный адаптер КР573РФ5 для Dumper Lite

Откройте `KR573RF5_Adapter.kicad_pro`, затем схему или плату. Это отдельный **полностью разведённый двухслойный адаптер 22,86 × 38,10 мм**, только для чтения на 5 В. Сверху — панелька DIP-24, снизу — два ряда круглых контактов «папа» для установки в DIP-28 панельку EPROM дампера. Шаг контактов 2,54 мм, расстояние между рядами 15,24 мм.

## Конструкция и детали

| Поз. | Деталь | Монтаж |
|---|---|---|
| J1 | Два ряда **1×14 круглых штырей**, подходящих для DIP-панельки, шаг 2,54 мм | Снизу, длинные контакты направлены вниз |
| J2 | Панелька DIP-24, 600 mil / 15,24 мм между рядами | Сверху; выемка совпадает с обозначением pin 1 |
| U1 | **SN74HCT245PW**, TSSOP-20, 4,4×6,5 мм, шаг 0,65 мм | Снизу |
| C1 | 100 нФ, X7R, ≥16 В, 0603 | Снизу, возле питания EPROM |
| C2 | 100 нФ, X7R, ≥16 В, 0603 | Снизу, возле питания U1 |
| C3 | 1 мкФ, X7R, ≥10 В, 0603 | Снизу |
| RN1, RN2 | **CAY16-473J4LF**, 4 независимых резистора по 47 кОм в каждой сборке, 3,2×1,6 мм, convex | Снизу; слабые подтяжки данных RF5 к +5 В |

Подойдёт HCT245 другого производителя с **той же распиновкой и TSSOP-20 4,4×6,5 мм**. Не заменяйте на обычный HC245: его входные уровни другие. Точная марка панельки и контактных полос не выбрана; сверяйте шаг, диаметр ножек, высоту и механические габариты перед покупкой. Квадратные штыри 0,64 мм от стандартной гребёнки нельзя силой вставлять в прецизионную DIP-панельку. Наиболее удобны круглые контакты примерно 0,45–0,50 мм или подходящие контакты DIP-переходника, рассчитанные на вашу панельку.

Верхняя панелька смещена на 2,54 мм вправо и на один шаг вниз относительно начала нижнего разъёма. Так её 24 отверстия не совпадают с 28 отверстиями нижнего разъёма и данные можно пропустить через буфер. Нижний буфер находится между рядами контактов. Плата без дополнительных крепёжных отверстий.

Пластиковая опора нижних контактных полос должна обеспечивать зазор **не менее 2,5 мм** между нижней поверхностью адаптера и верхней поверхностью панельки дампера: под адаптером стоят SMD-детали. Выбирайте длину контактов с достаточным рабочим заходом в панельку после учёта этого зазора. Выступающие **сверху** хвосты J1 перед установкой J2 обрежьте заподлицо и проверьте, что они не мешают корпусу J2. Две панельки/полосы изображены габаритными моделями; окончательная механическая совместимость требует проверки реальных деталей.

## Зачем нужен буфер

В опубликованном техническом листке КР573РФ5 указана минимальная выходная «1» 2,55 В. Вход ATmega328P при питании 5 В требует для гарантированной «1» минимум 0,6×VCC, то есть 3 В. Поэтому простая перепайка DIP-24 на DIP-28 не даёт гарантии чтения.

HCT245 принимает TTL-уровни: минимальная входная «1» 2 В по [Texas Instruments SN74HCT245](https://www.ti.com/lit/ds/symlink/sn74hct245.pdf), разделы 5–6. Его выходы питаются от тех же 5 В и подходят для ATmega. Порт A получает данные RF5, порт B подаёт их в дампер; DIR, pin 1, постоянно подключён к +5 В. OE#, pin 19, соединён с OE# EPROM и дампера, поэтому при HIGH буфер отключается. Резисторы подтяжки CE#/OE# уже есть в Lite и повторно на адаптере не установлены. Пороги ATmega: [Microchip ATmega328P, DC characteristics](https://ww1.microchip.com/downloads/aemDocuments/documents/MCU08/ProductDocuments/DataSheets/Atmel-7810-Automotive-Microcontrollers-ATmega328P_Datasheet.pdf).

Когда RF5 отключает свои выходы, восемь входов A буфера всё равно должны иметь определённый уровень. RN1/RN2 задают слабую подтяжку каждого RF5_D0…D7 к +5 В. При выходном LOW нагрузка одного резистора около 0,11 мА; при отключённой EPROM входы буфера остаются HIGH. Используются **изолированные** резисторы 1–8, 2–7, 3–6, 4–5, а не сборка с общей ножкой. Тип, шаг 0,8 мм и габариты проверены по [Bourns CAT/CAY16](https://www.bourns.com/docs/Product-Datasheets/CATCAY.pdf). Посадка KiCad имеет общую ширину земель 2,6 мм, в диапазоне рекомендованных 2,4–2,8 мм для CAY16-J4. На стороне MCU при отключённом буфере следует включить внутренние подтяжки входов данных.

## Распиновка

Нумерация J1 и J2 здесь дана **при взгляде сверху на собранный адаптер**, выемками вверх. Для DIP-28 слева сверху вниз идут 1…14, справа сверху вниз — 28…15. Для DIP-24 слева — 1…12, справа — 24…13. При взгляде на нижнюю сторону левый и правый ряды меняются местами визуально, номера электрических контактов не меняются.

| Вывод J2 / RF5 | Сигнал | Подключение |
|---|---|---|
| 1 | A7 | J1.3 |
| 2 | A6 | J1.4 |
| 3 | A5 | J1.5 |
| 4 | A4 | J1.6 |
| 5 | A3 | J1.7 |
| 6 | A2 | J1.8 |
| 7 | A1 | J1.9 |
| 8 | A0 | J1.10 |
| 9 | D0 | U1.2 → U1.18 → J1.11 |
| 10 | D1 | U1.3 → U1.17 → J1.12 |
| 11 | D2 | U1.4 → U1.16 → J1.13 |
| 12 | GND | J1.14, U1.10 |
| 13 | D3 | U1.5 → U1.15 → J1.15 |
| 14 | D4 | U1.6 → U1.14 → J1.16 |
| 15 | D5 | U1.7 → U1.13 → J1.17 |
| 16 | D6 | U1.8 → U1.12 → J1.18 |
| 17 | D7 | U1.9 → U1.11 → J1.19 |
| 18 | CE# | J1.20 |
| 19 | A10 | J1.21 |
| 20 | OE# | J1.22, U1.19 |
| 21 | VPP / Uпр | **+5 В для чтения**, J1.28 |
| 22 | A9 | J1.24 |
| 23 | A8 | J1.25 |
| 24 | VCC | +5 В, J1.28, U1.20 |

J1.1, .2, .23, .26, .27 не используются: это старшие адреса A15/A12/A11/A13/A14 у NM27C512. Память RF5 — **2048 байт**, адреса 0…2047. При чтении всех 65536 адресов NM27C512 её 2 КиБ будут повторяться 32 раза.

## Сборка и чтение

1. Паяйте нижние SMD-компоненты, проверьте питание и ориентацию U1.
2. Припаяйте круглые нижние контакты через выравнивающий шаблон с шагом 15,24 мм между рядами. Не нагревайте хорошую панельку дампера длительной пайкой через вставленные в неё контакты. Проверьте перпендикулярность и отсутствие перекоса.
3. Уберите верхние выступы J1 под корпусом J2, затем поставьте верхнюю панельку. При домашнем изготовлении без металлизации сначала выполните все переходы и нужные двухсторонние соединения сквозных площадок.
4. Без EPROM прозвоните питание, каждый адрес, CE# и OE#. RF5_D0…D7 и ROM_D0…D7 не должны быть замкнуты напрямую: между ними U1.
5. Вставьте адаптер в выключенный Lite, совместив первые выводы. Сначала проверьте на пустой панельке наличие 5 В на J2.21/.24 и GND на J2.12. Затем отключите питание и установите RF5.
6. Прошивка должна держать D0…D7 **входами с внутренними подтяжками**, выставлять адрес A0…A10, активировать CE#/OE#, ждать доступа и считывать байт. Для первого запуска используйте не менее 1 мкс после стабилизации адреса/управления; опубликованный листок указывает доступ до 420 нс, дополнительно есть задержка буфера. Читайте 2048 байт дважды и сравнивайте результаты.

Не подавайте 25 В на адаптер, не запускайте программирование, не включайте направление данных «MCU → EPROM». VPP RF5 на этой плате жёстко соединён с 5 В. В полной Stage 2 версии допустимость установки требует заранее проверенного режима чтения с питанием цели 5 В и отсутствием внешнего VPP; безопасный целевой проект для этого адаптера — Lite.

Существующие Stage 2 прошивка, профили и утилита не изменялись. Профиль RF5 в них остаётся заблокированным до получения исходного заводского документа; адаптер не добавляет автоматически поддержку RF5 в прошивку Lite. Здесь создана аппаратная плата для согласованного режима чтения, а не новый программный протокол.

## GND-полигоны для уменьшения травления

На обеих сторонах (`F.Cu` и `B.Cu`) добавлены и заполнены сплошные зоны сети **GND**. Зазор до других цепей — **0,25 мм**, минимальная ширина меди зоны — **0,25 мм**, отступ границы зоны от контура — **0,55 мм**. У площадок включены терморазвязки: зазор 0,25 мм, перемычки 0,30 мм. Изолированные участки, не связанные с GND, удаляются.

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
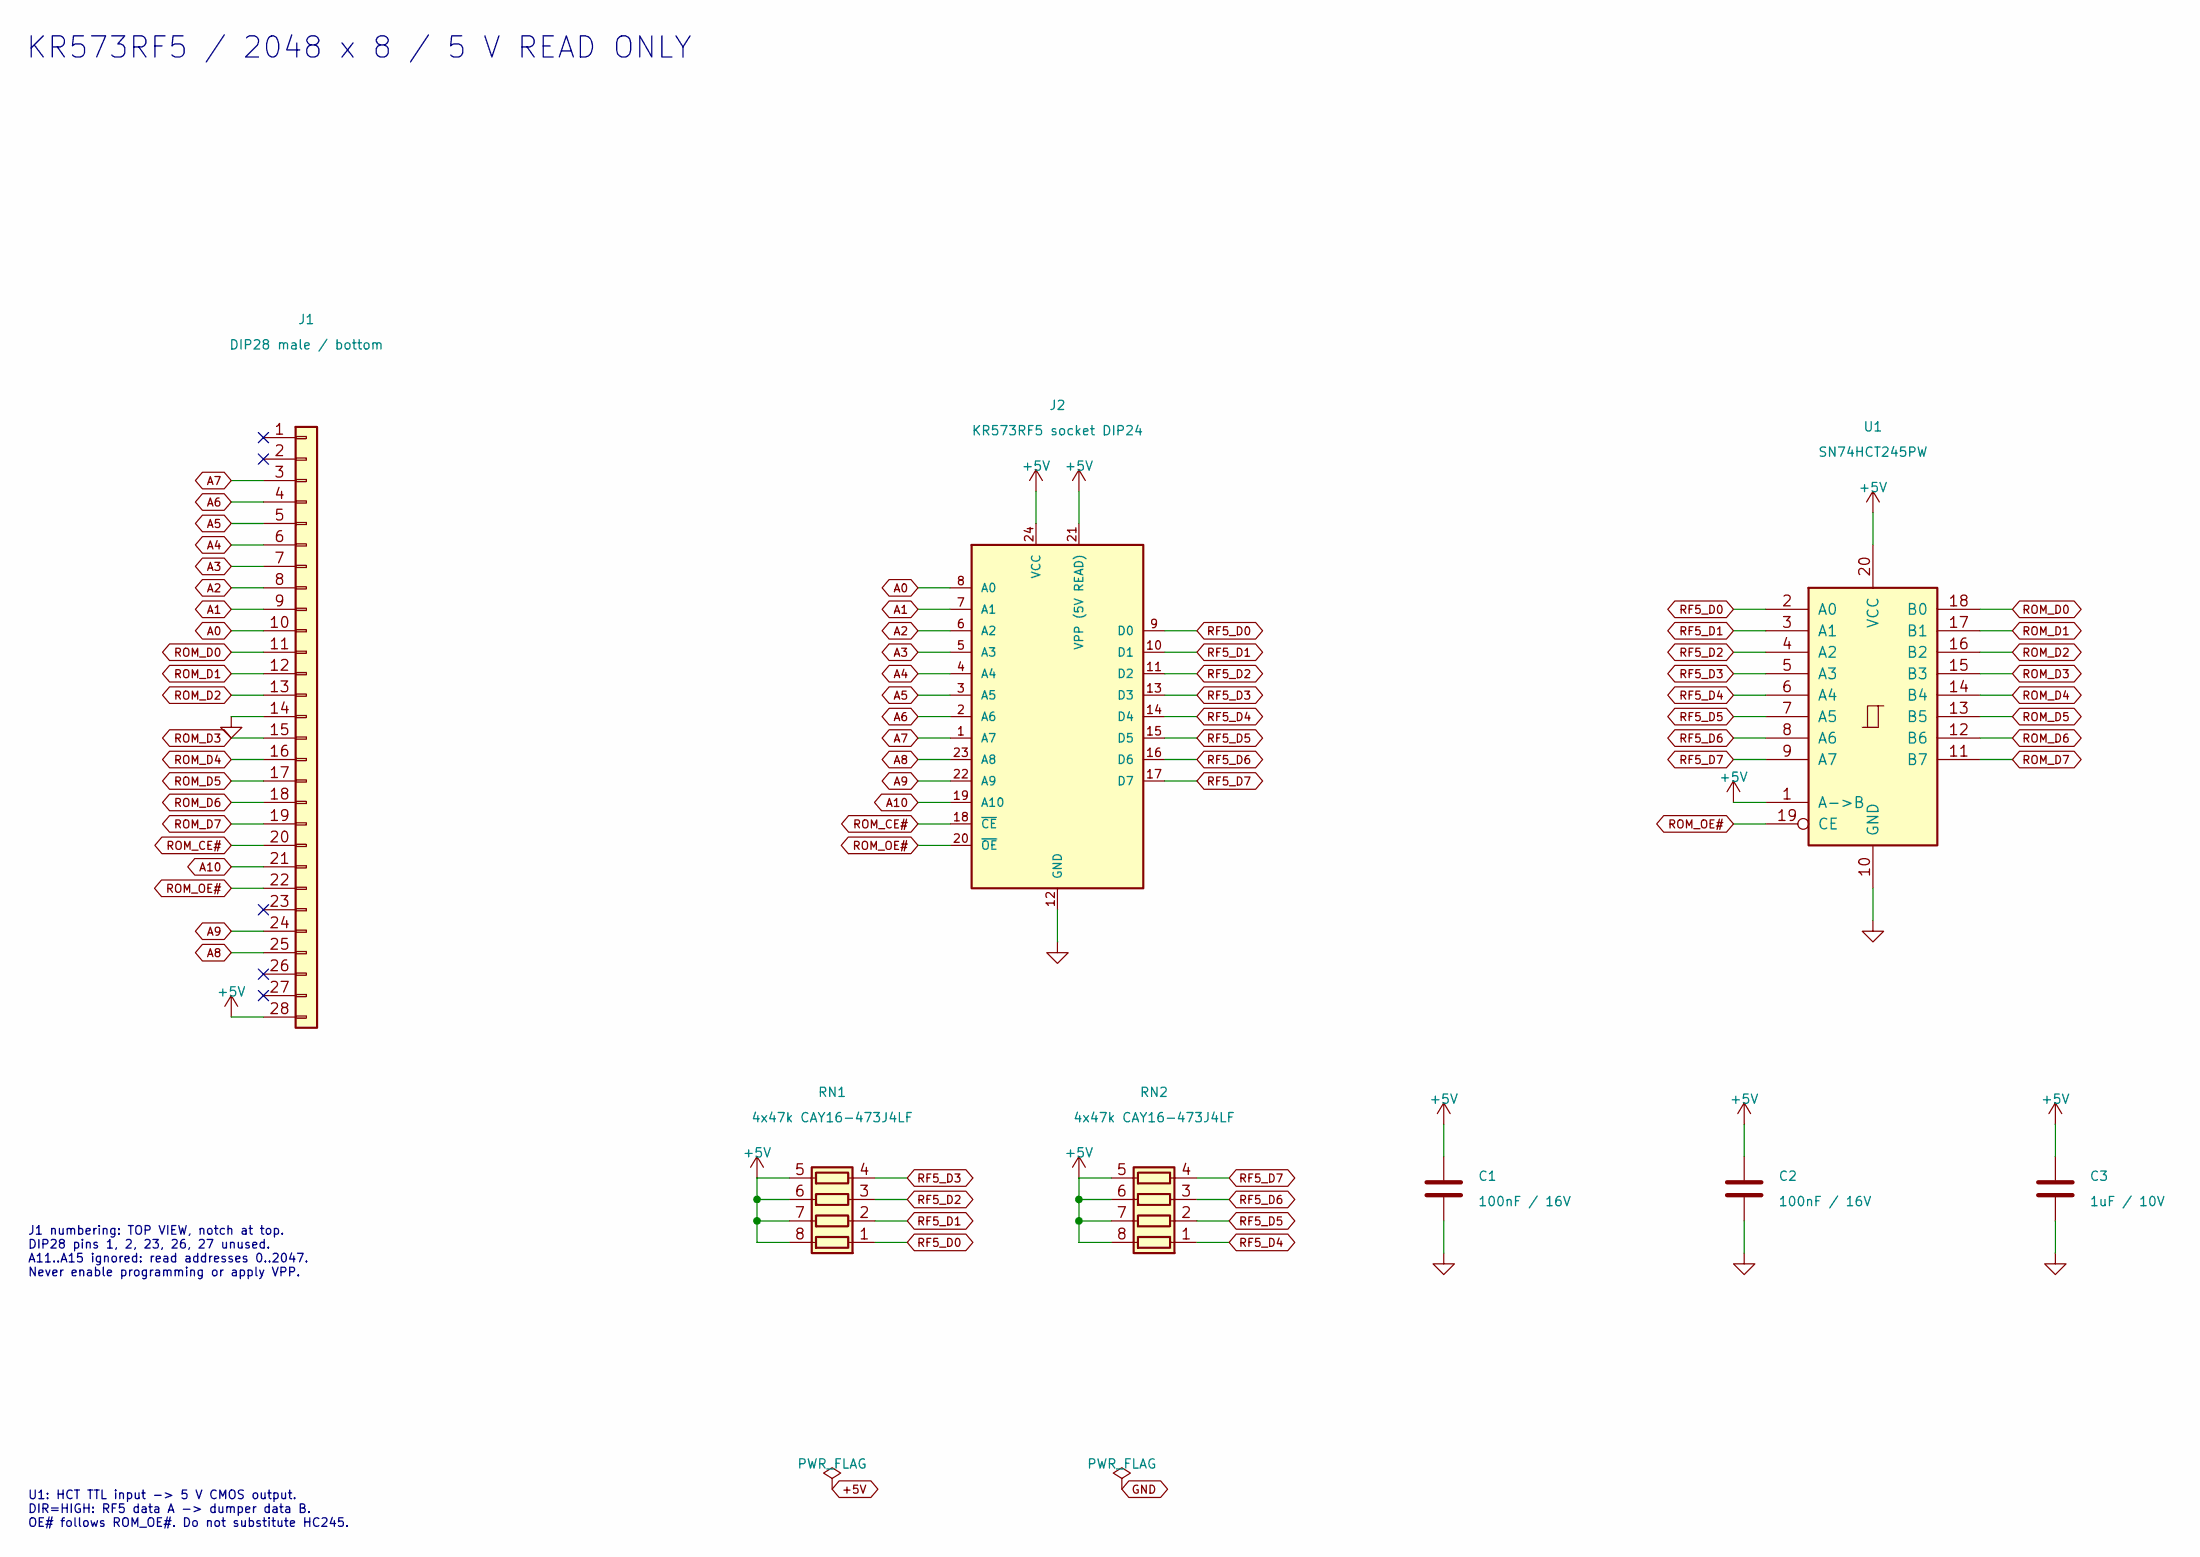
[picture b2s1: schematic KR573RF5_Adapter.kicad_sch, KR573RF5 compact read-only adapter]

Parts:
C1, C2: 100nF / 16V; C_0603_1608Metric
C3: 1uF / 10V; C_0603_1608Metric
J1: DIP28 male / bottom; DIP28_Male_RoundPins_Bottom
J2: KR573RF5 socket DIP24; DIP-24_W15.24mm_Socket_LongPads
RN1, RN2: 4x47k CAY16-473J4LF; R_Array_Convex_4x0603
U1: SN74HCT245PW; TSSOP-20_4.4x6.5mm_P0.65mm

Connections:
+5V: C1.1, C2.1, C3.1, J1.28, J2.21 (VPP (5V READ)), J2.24 (VCC), RN1.5 (R4.2), RN1.6 (R3.2), RN1.7 (R2.2), RN1.8 (R1.2), RN2.5 (R4.2), RN2.6 (R3.2), RN2.7 (R2.2), RN2.8 (R1.2), U1.1 (A->B), U1.20 (VCC)
A0: J1.10, J2.8 (A0)
A1: J1.9, J2.7 (A1)
A2: J1.8, J2.6 (A2)
A3: J1.7, J2.5 (A3)
A4: J1.6, J2.4 (A4)
A5: J1.5, J2.3 (A5)
A6: J1.4, J2.2 (A6)
A7: J1.3, J2.1 (A7)
A8: J1.25, J2.23 (A8)
A9: J1.24, J2.22 (A9)
A10: J1.21, J2.19 (A10)
GND: C1.2, C2.2, C3.2, J1.14, J2.12 (GND), U1.10 (GND)
RF5_D0: J2.9 (D0), RN1.1 (R1.1), U1.2 (A0)
RF5_D1: J2.10 (D1), RN1.2 (R2.1), U1.3 (A1)
RF5_D2: J2.11 (D2), RN1.3 (R3.1), U1.4 (A2)
RF5_D3: J2.13 (D3), RN1.4 (R4.1), U1.5 (A3)
RF5_D4: J2.14 (D4), RN2.1 (R1.1), U1.6 (A4)
RF5_D5: J2.15 (D5), RN2.2 (R2.1), U1.7 (A5)
RF5_D6: J2.16 (D6), RN2.3 (R3.1), U1.8 (A6)
RF5_D7: J2.17 (D7), RN2.4 (R4.1), U1.9 (A7)
ROM_CE#: J1.20, J2.18 (~CE)
ROM_D0: J1.11, U1.18 (B0)
ROM_D1: J1.12, U1.17 (B1)
ROM_D2: J1.13, U1.16 (B2)
ROM_D3: J1.15, U1.15 (B3)
ROM_D4: J1.16, U1.14 (B4)
ROM_D5: J1.17, U1.13 (B5)
ROM_D6: J1.18, U1.12 (B6)
ROM_D7: J1.19, U1.11 (B7)
ROM_OE#: J1.22, J2.20 (~OE), U1.19 (CE)

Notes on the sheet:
KR573RF5 / 2048 x 8 / 5 V READ ONLY
J1 numbering: TOP VIEW, notch at top. DIP28 pins 1, 2, 23, 26, 27 unused. A11..A15 ignored: read addresses 0..2047. Never enable programming or apply VPP.
U1: HCT TTL input -> 5 V CMOS output. DIR=HIGH: RF5 data A -> dumper data B. OE# follows ROM_OE#. Do not substitute HC245.

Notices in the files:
Adapter-KR573RF5/README.md:
Стандартные символы и модели корпусов KiCad имеют лицензию KiCad Libraries CC BY-SA 4.0 с исключением для электронных проектов.
